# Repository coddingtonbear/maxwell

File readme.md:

# Maxwell: Bicycle Electrification

See my little blog post about this here: [http://coddingtonbear.net/maxwell-bicycle-electrification/](http://coddingtonbear.net/maxwell-bicycle-electrification/).

I have a bicycle dynamo on my bike, a rudimentary understanding of electronics, and a bunch of neopixels, gps, and bluetooth modules to use.  This is what happens when those things combine.

Maxwell is a two-part bike computer I've designed to allow me to do a few things:

* Light and control neopixel LEDs wrapped around my bike for added safety while biking at night, and added fun when biking with groups.
* Charge an easily-swappable 18650 Li-On cell for potential use when bike touring.
* Gather and transmit GPS coordinates for display on the internet somewhere.
* Display status information including my current speed, battery voltage, and current consumption, as well as disable or enable bike features including, most importantly, disabling and enabling the LEDs from a small screen mounted at the front of the bike.
* Send interesting data for display on the internet for completely impractical reasons.

The "remote" unit is based around the STM32F103CB microcontroller, and the "base" unit is based around its slightly-more-full-featured brother, the STM32F103RE.  Both communicate with one another over a CANBus (routed through two of the conductors in a length of ethernet cable) to share status information and emit/handle commands.

## Schematics

### Main

### LTE Module

### Head Unit (Remote)

## Errata

Checked items indicate errata that have been corrected in the schematic.

### Maxwell

None as of rev 1.7.

### Maxwell-remote

* [ ] Incorrect diode footprint for polarity protection.  There also might be a power deliver problem through those diodes.  Investigate that the selected mosftet is ON at Vgs -3.3.
* [ ] I think the gerbers I generated originally may have excluded the rear solder mask, as the resistors and vias were covered.
* [ ] Board-to-board interconnect should probably either not use an FPC connector, or use multiple conductors for power/ground.  I had to build a workaround connector for transferring power between the two boards.
* [ ] Resistor R2 of maxwell-remote-2 isn't really necessary; it could be connected directly to VCC.

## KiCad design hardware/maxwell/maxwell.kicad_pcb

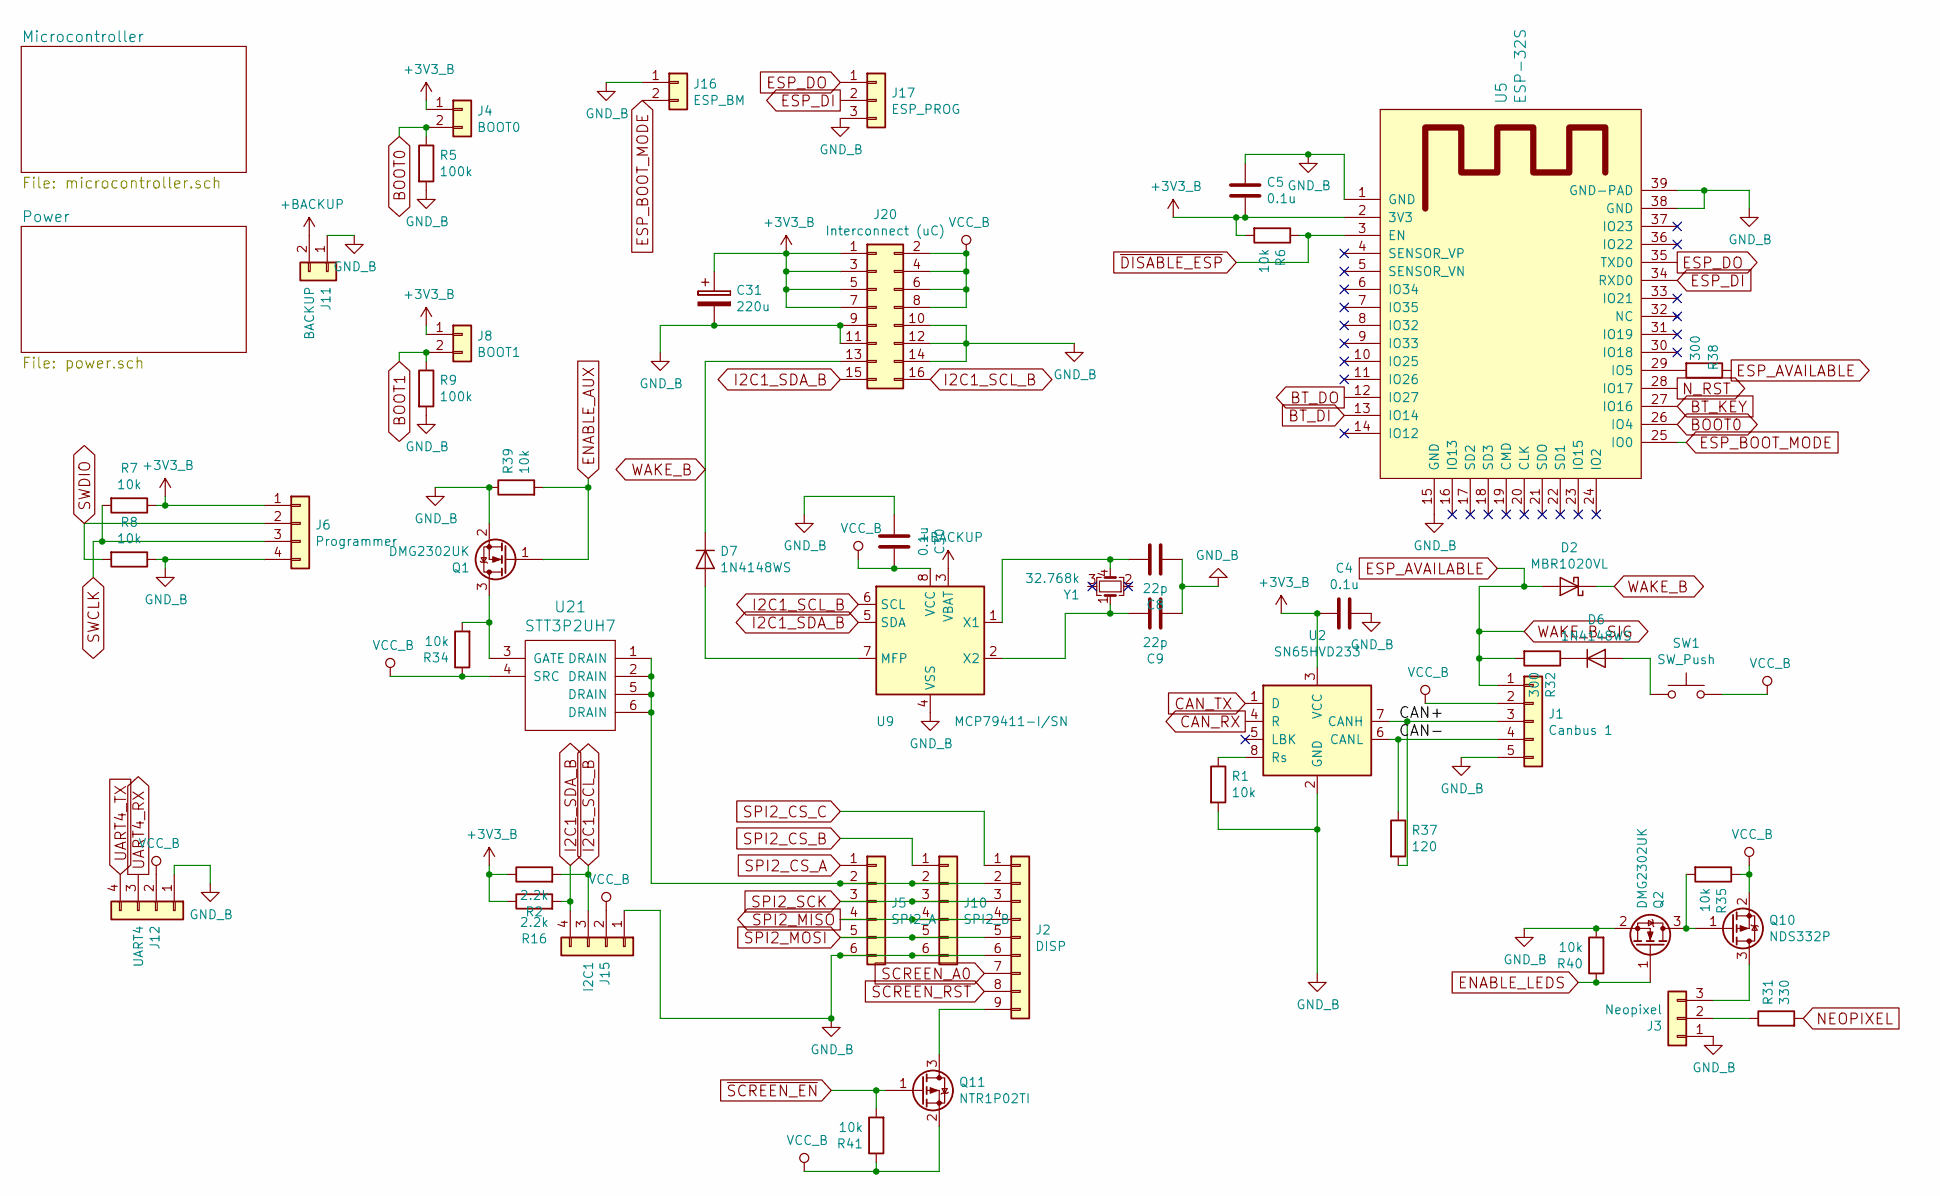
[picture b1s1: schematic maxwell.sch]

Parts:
C4, C5, C30: 0.1u; 0805_Milling
C8, C9: 22p; 0805_Milling
C31: 220u; CP_Tantalum_Case-C_EIA-6032-28_Milling
D2: MBR1020VL; D_SOD-123_LargePads
D6, D7: 1N4148WS; D_SOD-323_HandSoldering
J1: Canbus 1; JST_XH_B05B-XH-A_05x2.50mm_Straight_LargePads
J2: DISP; JST_XH_B09B-XH-A_1x09_P2.50mm_Straight_LargePads
J3: Neopixel; JST_XH_B03B-XH-A_03x2.50mm_Straight_LargePads
J4: BOOT0; Pin_Header_Straight_1x02_Pitch1.27mm_JMP
J5: SPI2_A; JST_XH_B06B-XH-A_06x2.50mm_Straight_LargePads
J6: Programmer; Pin_Header_Straight_1x04_Pitch2.54mm_LargePads
J8: BOOT1; Pin_Header_Straight_1x02_Pitch1.27mm_JMP
J10: SPI2_B; JST_XH_B06B-XH-A_06x2.50mm_Straight_LargePads
J11: BACKUP; JST_XH_B02B-XH-A_02x2.50mm_Straight_LargePads
J12: UART4; JST_XH_B04B-XH-A_04x2.50mm_Straight_LargePads
J15: I2C1; JST_XH_B04B-XH-A_04x2.50mm_Straight_LargePads
J16: ESP_BM; Pin_Header_Straight_1x02_Pitch1.27mm_JMP
J17: ESP_PROG; JST_XH_B03B-XH-A_03x2.50mm_Straight_LargePads
J20: Interconnect (uC); IDC-Header_2x08_P2.54mm_Vertical_Largepads
Q1, Q2: DMG2302UK; SOT-23_LargePads
Q10: NDS332P; SOT-23_LargePads
Q11: NTR1P02TI; SOT-23_LargePads
R1, R6, R7, R8, R34, R35, R39, R40, R41: 10k; 0805_Milling
R2, R16: 2.2k; 0805_Milling
R5, R9: 100k; 0805_Milling
R31: 330; 0805_Milling
R32, R38: 300; 0805_Milling
R37: 120; 0805_Milling
SW1: SW_Push; SMD_MINI_BLACK_TACTILE_SWITCH
U2: SN65HVD233; SOIC-8_3.9x4.9mm_P1.27mm_LargePads
U5: ESP-32S
U9: MCP79411-I/SN; SOIC-8_3.9x4.9mm_P1.27mm_LargePads
U21: STT3P2UH7; SOT-23-6_Handsoldering
Y1: 32.768k; Crystal_SMD_SeikoEpson_MC306-4Pin_8.0x3.2mm_HandSoldering

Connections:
+3V3_B: C4.2, C5.2, C31.1, J4.1, J6.1, J8.1, J20.1, J20.3, J20.5, J20.7, R2.1, R6.2, R7.1, R16.1, U2.3 (VCC), U5.2 (3V3); also elsewhere on the board
+BACKUP: J11.2, U9.3 (VBAT)
/CAN+: J1.3, R37.2, U2.7 (CANH)
/CAN-: J1.4, R37.1, U2.6 (CANL)
BOOT0: J4.2, R5.1, U5.26 (IO4); also elsewhere on the board
BOOT1: J8.2, R9.1; also elsewhere on the board
BT_DI: U5.13 (IO14); also elsewhere on the board
BT_DO: U5.12 (IO27); also elsewhere on the board
BT_KEY: U5.27 (IO16); also elsewhere on the board
CAN_RX: U2.4 (R); also elsewhere on the board
CAN_TX: U2.1 (D); also elsewhere on the board
ENABLE_AUX: Q1.1 (G), R39.2; also elsewhere on the board
ENABLE_LEDS: Q2.1 (G), R40.1; also elsewhere on the board
ESP_AVAILABLE: D2.2 (A), J1.1, R32.2, R38.1; also elsewhere on the board
ESP_BOOT_MODE: J16.2, U5.25 (IO0)
ESP_DI: J17.2, U5.34 (RXD0)
ESP_DO: J17.1, U5.35 (TXD0)
GND_B: C4.1, C5.1, C8.2, C9.2, C30.2, C31.2, J1.5, J2.6, J3.1, J5.6, J6.4, J10.6, J11.1, J12.1, J15.1, J16.1, J17.3, J20.9, J20.10, J20.11, J20.12, J20.14, Q1.2 (S), Q2.2 (S), R1.2, R5.2, R8.1, R9.2, R39.1, R40.2, U2.2 (GND), U5.1 (GND), U5.15 (GND), U5.38 (GND), U5.39 (GND-PAD), U9.4 (VSS); also elsewhere on the board
I2C1_SCL_B: J15.3, J20.16, R2.2, U9.6 (SCL); also elsewhere on the board
I2C1_SDA_B: J15.4, J20.15, R16.2, U9.5 (SDA); also elsewhere on the board
NEOPIXEL: R31.2; also elsewhere on the board
N_RST: U5.28 (IO17); also elsewhere on the board
unnamed: C8.1, U9.1 (X1), Y1.4
unnamed: C9.1, U9.2 (X2), Y1.1
unnamed: D6.1 (K), R32.1
unnamed: D6.2 (A), SW1.1
unnamed: D7.2 (A), U9.7 (MFP)
unnamed: J2.9, Q11.3 (D)
unnamed: J3.2, R31.1
unnamed: J3.3, Q10.3 (D)
unnamed: J2.2, J5.2, J10.2, U21.1 (DRAIN), U21.2 (DRAIN), U21.5 (DRAIN), U21.6 (DRAIN)
unnamed: Q1.3 (D), R34.2, U21.3 (GATE)
unnamed: Q2.3 (D), Q10.1 (G), R35.2
unnamed: R1.1, U2.8 (Rs)
unnamed: R38.2, U5.29 (IO5)
SCREEN_A0: J2.7; also elsewhere on the board
SCREEN_RST: J2.8; also elsewhere on the board
SPI2_CS_A: J5.1; also elsewhere on the board
SPI2_CS_B: J10.1; also elsewhere on the board
SPI2_CS_C: J2.1; also elsewhere on the board
SPI2_MISO: J2.4, J5.4, J10.4; also elsewhere on the board
SPI2_MOSI: J2.5, J5.5, J10.5; also elsewhere on the board
SPI2_SCK: J2.3, J5.3, J10.3; also elsewhere on the board
SWCLK: J6.3, R7.2; also elsewhere on the board
SWDIO: J6.2, R8.2; also elsewhere on the board
UART4_RX: J12.3; also elsewhere on the board
UART4_TX: J12.4; also elsewhere on the board
VCC_B: C30.1, J1.2, J12.2, J15.2, J20.2, J20.4, J20.6, J20.8, Q10.2 (S), Q11.2 (S), R34.1, R35.1, R41.1, SW1.2, U9.8 (VCC), U21.4 (SRC)
WAKE_B: D2.1 (K), D7.1 (K), J20.13
~DISABLE_ESP: R6.1, U5.3 (EN); also elsewhere on the board
~SCREEN_EN: Q11.1 (G), R41.2; also elsewhere on the board

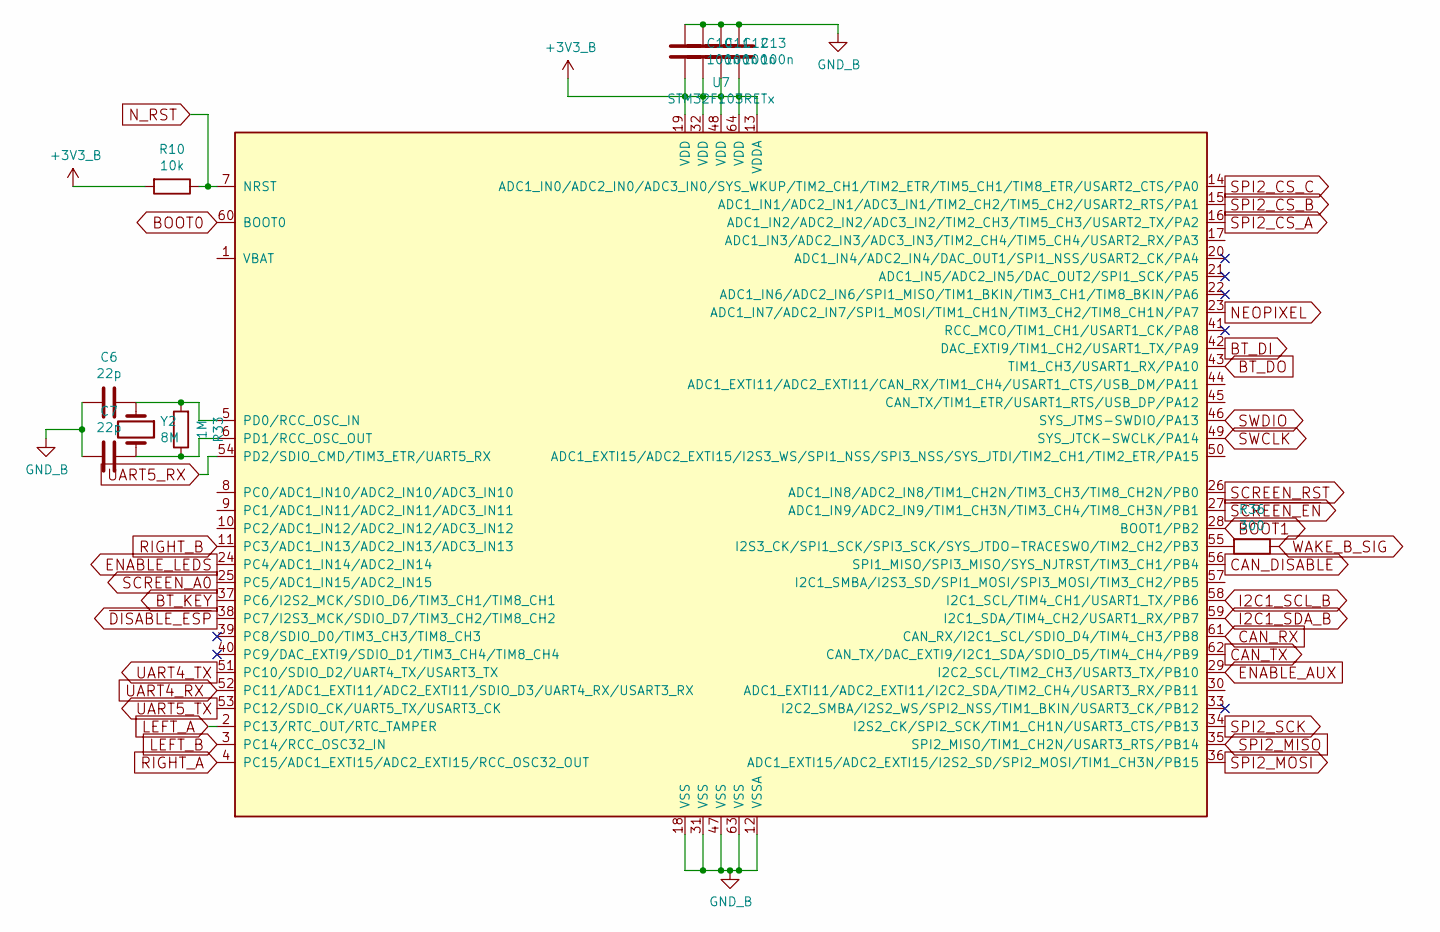
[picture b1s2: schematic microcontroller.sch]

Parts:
C6, C7: 22p; 0805_Milling
C10, C11, C12, C13: 100n; 0805_Milling
R10: 10k; 0805_Milling
R33: 1M; 0805_Milling
R36: 300; 0805_Milling
U7: STM32F103RETx; QFP64-1.27MM-CASTELLATED
Y2: 8M; Abracon-ABM2_LargePads

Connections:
+3V3_B: C10.1, C11.1, C12.1, C13.1, R10.2, U7.13 (VDDA), U7.19 (VDD), U7.32 (VDD), U7.48 (VDD), U7.64 (VDD); also elsewhere on the board
BOOT0: U7.60 (BOOT0); also elsewhere on the board
BOOT1: U7.28 (BOOT1/PB2); also elsewhere on the board
BT_DI: U7.42 (DAC_EXTI9/TIM1_CH2/USART1_TX/PA9); also elsewhere on the board
BT_DO: U7.43 (TIM1_CH3/USART1_RX/PA10); also elsewhere on the board
BT_KEY: U7.37 (PC6/I2S2_MCK/SDIO_D6/TIM3_CH1/TIM8_CH1); also elsewhere on the board
CAN_DISABLE: U7.56 (SPI1_MISO/SPI3_MISO/SYS_NJTRST/TIM3_CH1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)
CAN_RX: U7.61 (CAN_RX/I2C1_SCL/SDIO_D4/TIM4_CH3/PB8); also elsewhere on the board
CAN_TX: U7.62 (CAN_TX/DAC_EXTI9/I2C1_SDA/SDIO_D5/TIM4_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); also elsewhere on the board
ENABLE_AUX: U7.29 (I2C2_SCL/TIM2_CH3/USART3_TX/PB10); also elsewhere on the board
ENABLE_LEDS: U7.24 (PC4/ADC1_IN14/ADC2_IN14); also elsewhere on the board
ESP_AVAILABLE: R36.1; also elsewhere on the board
GND_B: C6.2, C7.2, C10.2, C11.2, C12.2, C13.2, U7.12 (VSSA), U7.18 (VSS), U7.31 (VSS), U7.47 (VSS), U7.63 (VSS); also elsewhere on the board
I2C1_SCL_B: U7.58 (I2C1_SCL/TIM4_CH1/USART1_TX/PB6); also elsewhere on the board
I2C1_SDA_B: U7.59 (I2C1_SDA/TIM4_CH2/USART1_RX/PB7); also elsewhere on the board
LEFT_A: U7.2 (PC13/RTC_OUT/RTC_TAMPER); also elsewhere on the board
LEFT_B: U7.3 (PC14/RCC_OSC32_IN); also elsewhere on the board
NEOPIXEL: U7.23 (ADC1_IN7/ADC2_IN7/SPI1_MOSI/TIM1_CH1N/T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); also elsewhere on the board
N_RST: R10.1, U7.7 (NRST); also elsewhere on the board
unnamed: C6.1, R33.2, U7.5 (PD0/RCC_OSC_IN), Y2.1
unnamed: C7.1, R33.1, U7.6 (PD1/RCC_OSC_OUT), Y2.2
unnamed: R36.2, U7.55 (I2S3_CK/SPI1_SCK/SPI3_SCK/SYS_JTDO-TRAC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)
RIGHT_A: U7.4 (PC15/ADC1_EXTI15/ADC2_EXTI15/RCC_OSC32_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); also elsewhere on the board
RIGHT_B: U7.11 (PC3/ADC1_IN13/ADC2_IN13/ADC3_IN13); also elsewhere on the board
SCREEN_A0: U7.25 (PC5/ADC1_IN15/ADC2_IN15); also elsewhere on the board
SCREEN_RST: U7.26 (ADC1_IN8/ADC2_IN8/TIM1_CH2N/TIM3_CH3/TI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); also elsewhere on the board
SPI2_CS_A: U7.16 (ADC1_IN2/ADC2_IN2/ADC3_IN2/TIM2_CH3/TIM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); also elsewhere on the board
SPI2_CS_B: U7.15 (ADC1_IN1/ADC2_IN1/ADC3_IN1/TIM2_CH2/TIM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); also elsewhere on the board
SPI2_CS_C: U7.14 (ADC1_IN0/ADC2_IN0/ADC3_IN0/SYS_WKUP/TIM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); also elsewhere on the board
SPI2_MISO: U7.35 (SPI2_MISO/TIM1_CH2N/USART3_RTS/PB14); also elsewhere on the board
SPI2_MOSI: U7.36 (ADC1_EXTI15/ADC2_EXTI15/I2S2_SD/SPI2_MO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); also elsewhere on the board
SPI2_SCK: U7.34 (I2S2_CK/SPI2_SCK/TIM1_CH1N/USART3_CTS/P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); also elsewhere on the board
SWCLK: U7.49 (SYS_JTCK-SWCLK/PA14); also elsewhere on the board
SWDIO: U7.46 (SYS_JTMS-SWDIO/PA13); also elsewhere on the board
UART4_RX: U7.52 (PC11/ADC1_EXTI11/ADC2_EXTI11/SDIO_D3/UA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); also elsewhere on the board
UART4_TX: U7.51 (PC10/SDIO_D2/UART4_TX/USART3_TX); also elsewhere on the board
UART5_RX: U7.54 (PD2/SDIO_CMD/TIM3_ETR/UART5_RX)
UART5_TX: U7.53 (PC12/SDIO_CK/UART5_TX/USART3_CK)
~DISABLE_ESP: U7.38 (PC7/I2S3_MCK/SDIO_D7/TIM3_CH2/TIM8_CH2); also elsewhere on the board
~SCREEN_EN: U7.27 (ADC1_IN9/ADC2_IN9/TIM1_CH3N/TIM3_CH4/TI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); also elsewhere on the board

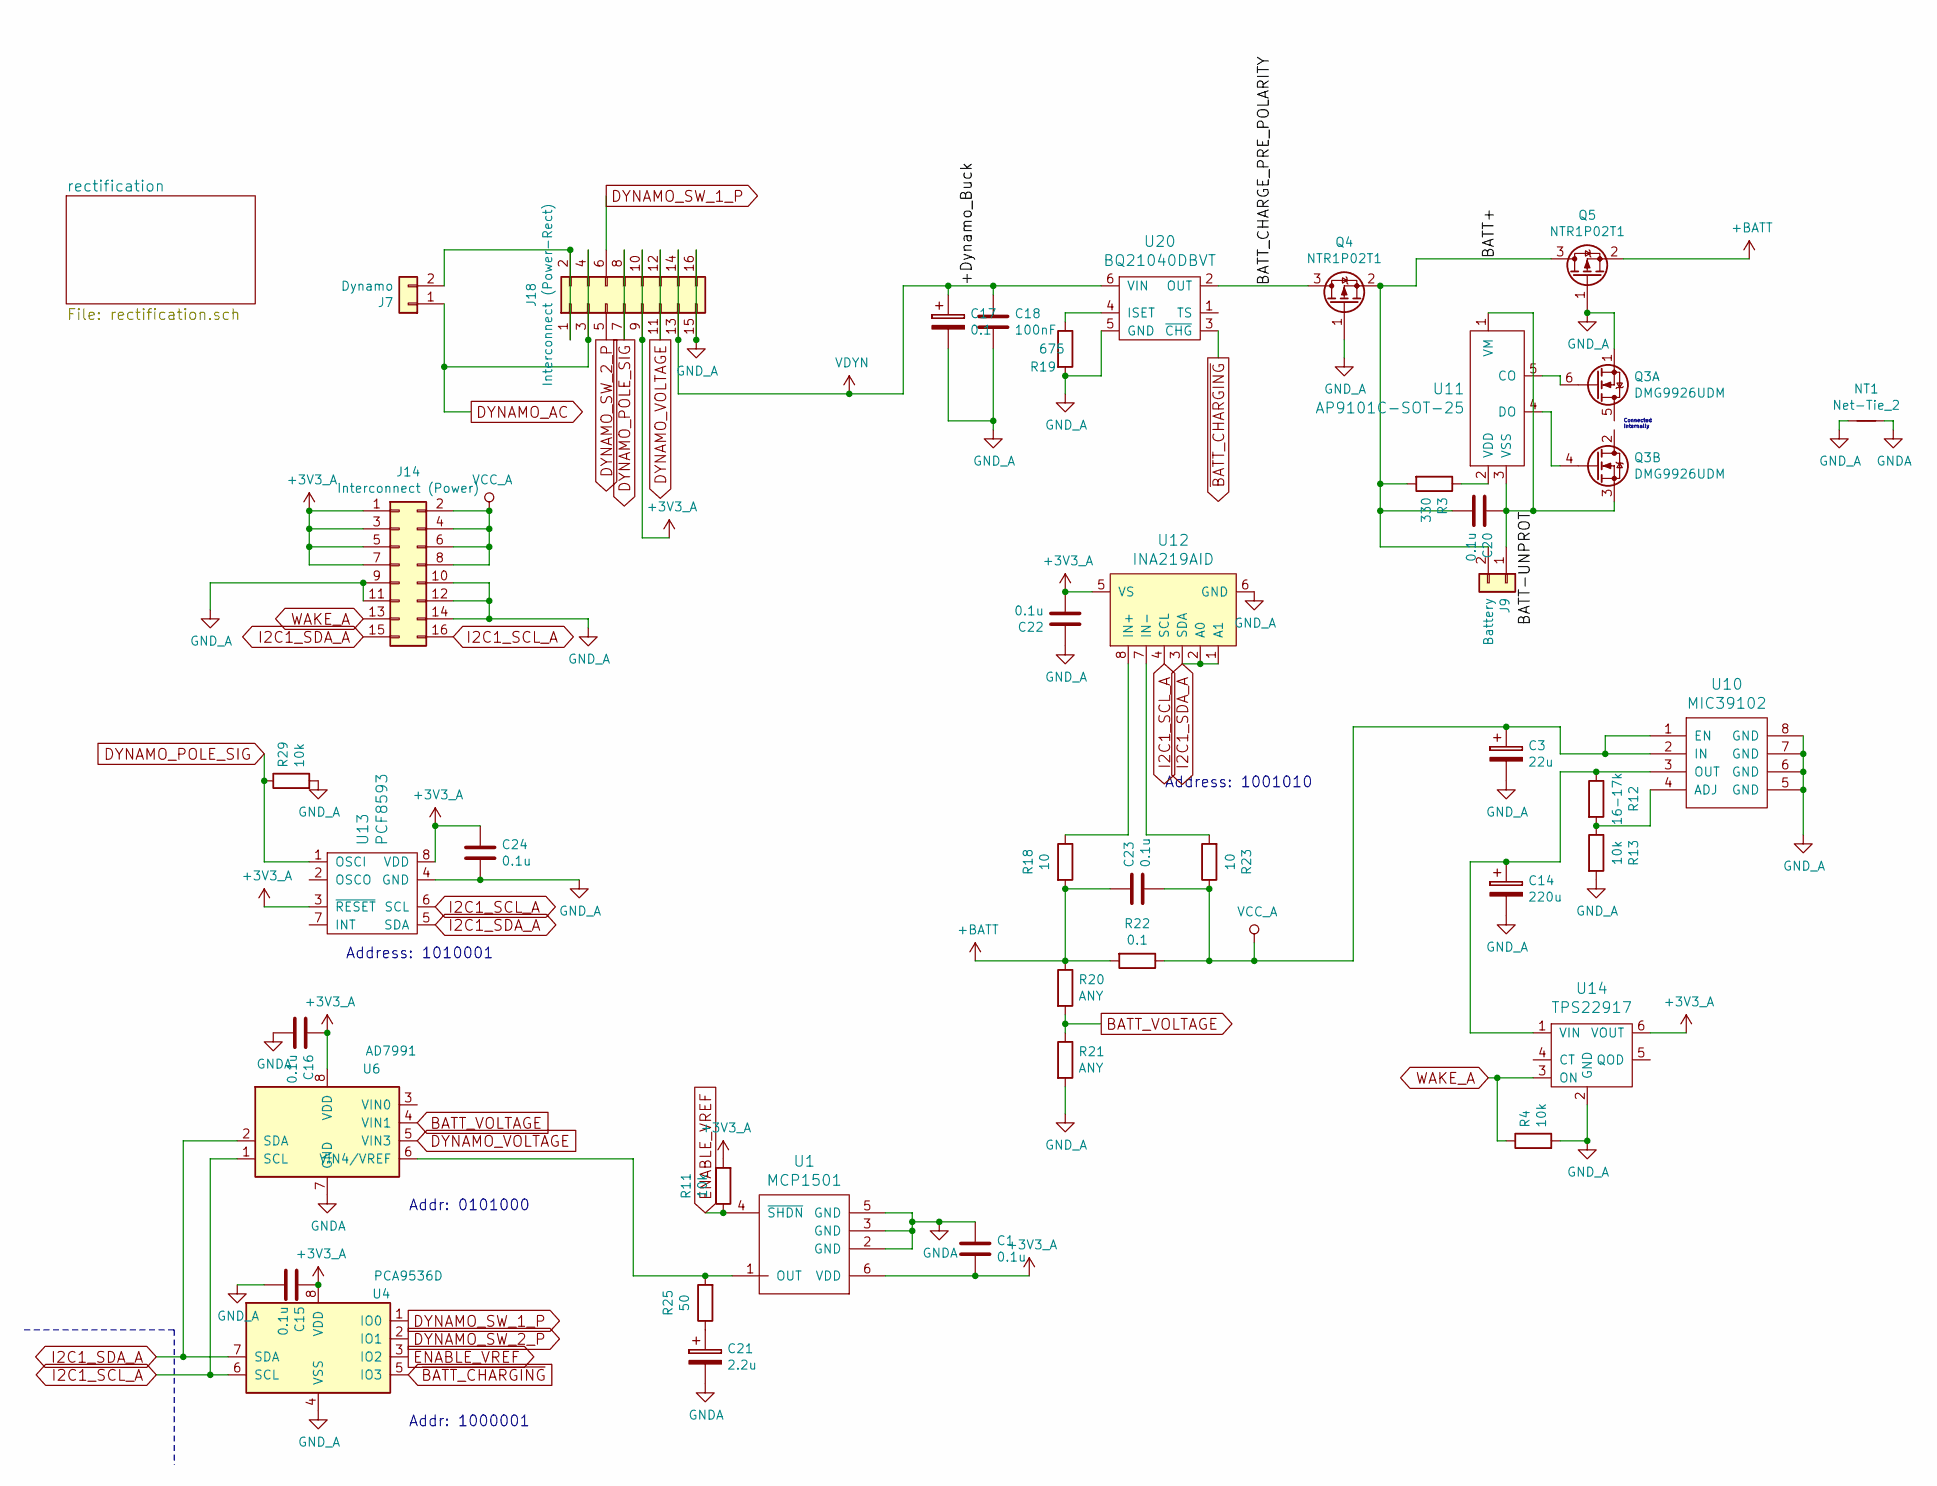
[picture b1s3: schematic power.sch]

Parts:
C1, C15, C16, C20, C22, C23, C24: 0.1u; 0805_Milling
C3: 22u; CP_Tantalum_Case-C_EIA-6032-28_Milling
C14: 220u; CP_Tantalum_Case-C_EIA-6032-28_Milling
C17: 0.1; JST_XH_B02B-XH-A_02x2.50mm_Straight_LargePads
C18: 100nF; 0805_Milling
C21: 2.2u; CP_Tantalum_Case-C_EIA-6032-28_Milling
J7: Dynamo; JST_XH_B02B-XH-A_02x2.50mm_Straight_LargePads
J9: Battery; JST_XH_B02B-XH-A_02x2.50mm_Straight_LargePads
J14: Interconnect (Power); IDC-Header_2x08_P2.54mm_Vertical_Largepads
J18: Interconnect (Power-Rect); PinHeader_2x08_P2.54mm_Vertical_LargePads
NT1: Net-Tie_2; NetTie-2_SMD_Pad0.5mm
Q3: DMG9926UDM; SOT-23-6_Handsoldering
Q4, Q5: NTR1P02T1; SOT-23_LargePads
R3: 330; 0805_Milling
R4, R11, R13, R29: 10k; 0805_Milling
R12: 16-17k; 0805_Milling
R18, R23: 10; 0805_Milling
R19: 675; 0805_Milling
R20, R21: ANY; 0805_Milling
R22: 0.1; 0805_Milling
R25: 50; 0805_Milling
U1: MCP1501; TSOT-23-6_HandSoldering
U4: PCA9536D; SOIC-8_3.9x4.9mm_P1.27mm_LargePads
U6: AD7991; SOT-23-8_Handsoldering
U10: MIC39102; SOIC-8_3.9x4.9mm_P1.27mm_LargePads
U11: AP9101C-SOT-25; SOT-23-5_HandSoldering
U12: INA219AID; SOIC-8_3.9x4.9mm_P1.27mm_LargePads; MPN INA219AIDCNR; Digi-Key_PN 296-23770-1-ND
U13: PCF8593; SOIC-8_3.9x4.9mm_P1.27mm_LargePads
U14: TPS22917; SOT-23-6_Handsoldering
U20: BQ21040DBVT; SOT-23-6_Handsoldering

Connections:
+3V3_U: C14.1, R12.1, U10.3 (OUT), U14.1 (VIN)
+BATT: C23.2, Q5.2 (S), R18.2, R20.1, R22.2
/Power/BATT+: C20.1, J9.2, Q4.2 (S), Q5.3 (D), R3.2
/Power/BATT-UNPROT: C20.2, J9.1, Q3.3 (S), U11.1 (VM), U11.3 (VSS)
/Power/BATT_CHARGE_PRE_POLARITY: Q4.3 (D), U20.2 (OUT)
BATT_VOLTAGE: R20.2, R21.1, U6.4 (VIN1)
CHARGE_VOLTAGE: J18.11, J18.12, U6.5 (VIN3)
DYNAMO_AC: J7.1, J18.3, J18.4
DYNAMO_POLE_SIG: J18.7, J18.8, R29.1, U13.1 (OSCI)
GNDA: C1.2, C16.1, C21.2, NT1.2, U1.2 (GND), U1.3 (GND), U1.5 (GND), U6.7 (GND)
GND_A: C3.2, C14.2, C15.1, C17.2, C18.1, C22.2, C24.1, J14.9, J14.10, J14.11, J14.12, J14.14, J18.15, J18.16, NT1.1, Q3.1 (S), Q4.1 (G), Q5.1 (G), R4.2, R13.2, R19.2, R21.2, R29.2, U4.4 (VSS), U10.5 (GND), U10.6 (GND), U10.7 (GND), U10.8 (GND), U12.6 (GND), U13.4 (GND), U14.2 (GND), U20.5 (GND); also elsewhere on the board
I2C1_SCL_A: J14.16, U4.6 (SCL), U6.1 (SCL), U12.4 (SCL), U13.6 (SCL); also elsewhere on the board
I2C1_SDA_A: J14.15, U4.7 (SDA), U6.2 (SDA), U12.1 (A1), U12.2 (A0), U12.3 (SDA), U13.5 (SDA); also elsewhere on the board
unnamed: C21.1, R25.1
unnamed: J7.2, J18.1, J18.2
unnamed: Q3.4 (G), U11.4 (DO)
unnamed: Q3.6 (G), U11.5 (CO)
unnamed: R3.1, U11.2 (VDD)
unnamed: R12.2, R13.1, U10.4 (ADJ)
unnamed: R18.1, U12.8 (IN+)
unnamed: R19.1, U20.4 (ISET)
unnamed: R23.2, U12.7 (IN-)
unnamed: R25.2, U1.1 (OUT), U6.6 (VIN4/VREF)
VCC_A: C3.1, C23.1, J14.2, J14.4, J14.6, J14.8, R22.1, R23.1, U10.1 (EN), U10.2 (IN)
VDYN: C17.1, C18.2, J18.13, J18.14, U20.6 (VIN)
WAKE_A: J14.13, R4.1, U14.3 (ON)

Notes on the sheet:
Addr: 1000001
Addr: 0101000
Connected Internally
Address: 1001010
Address: 1010001

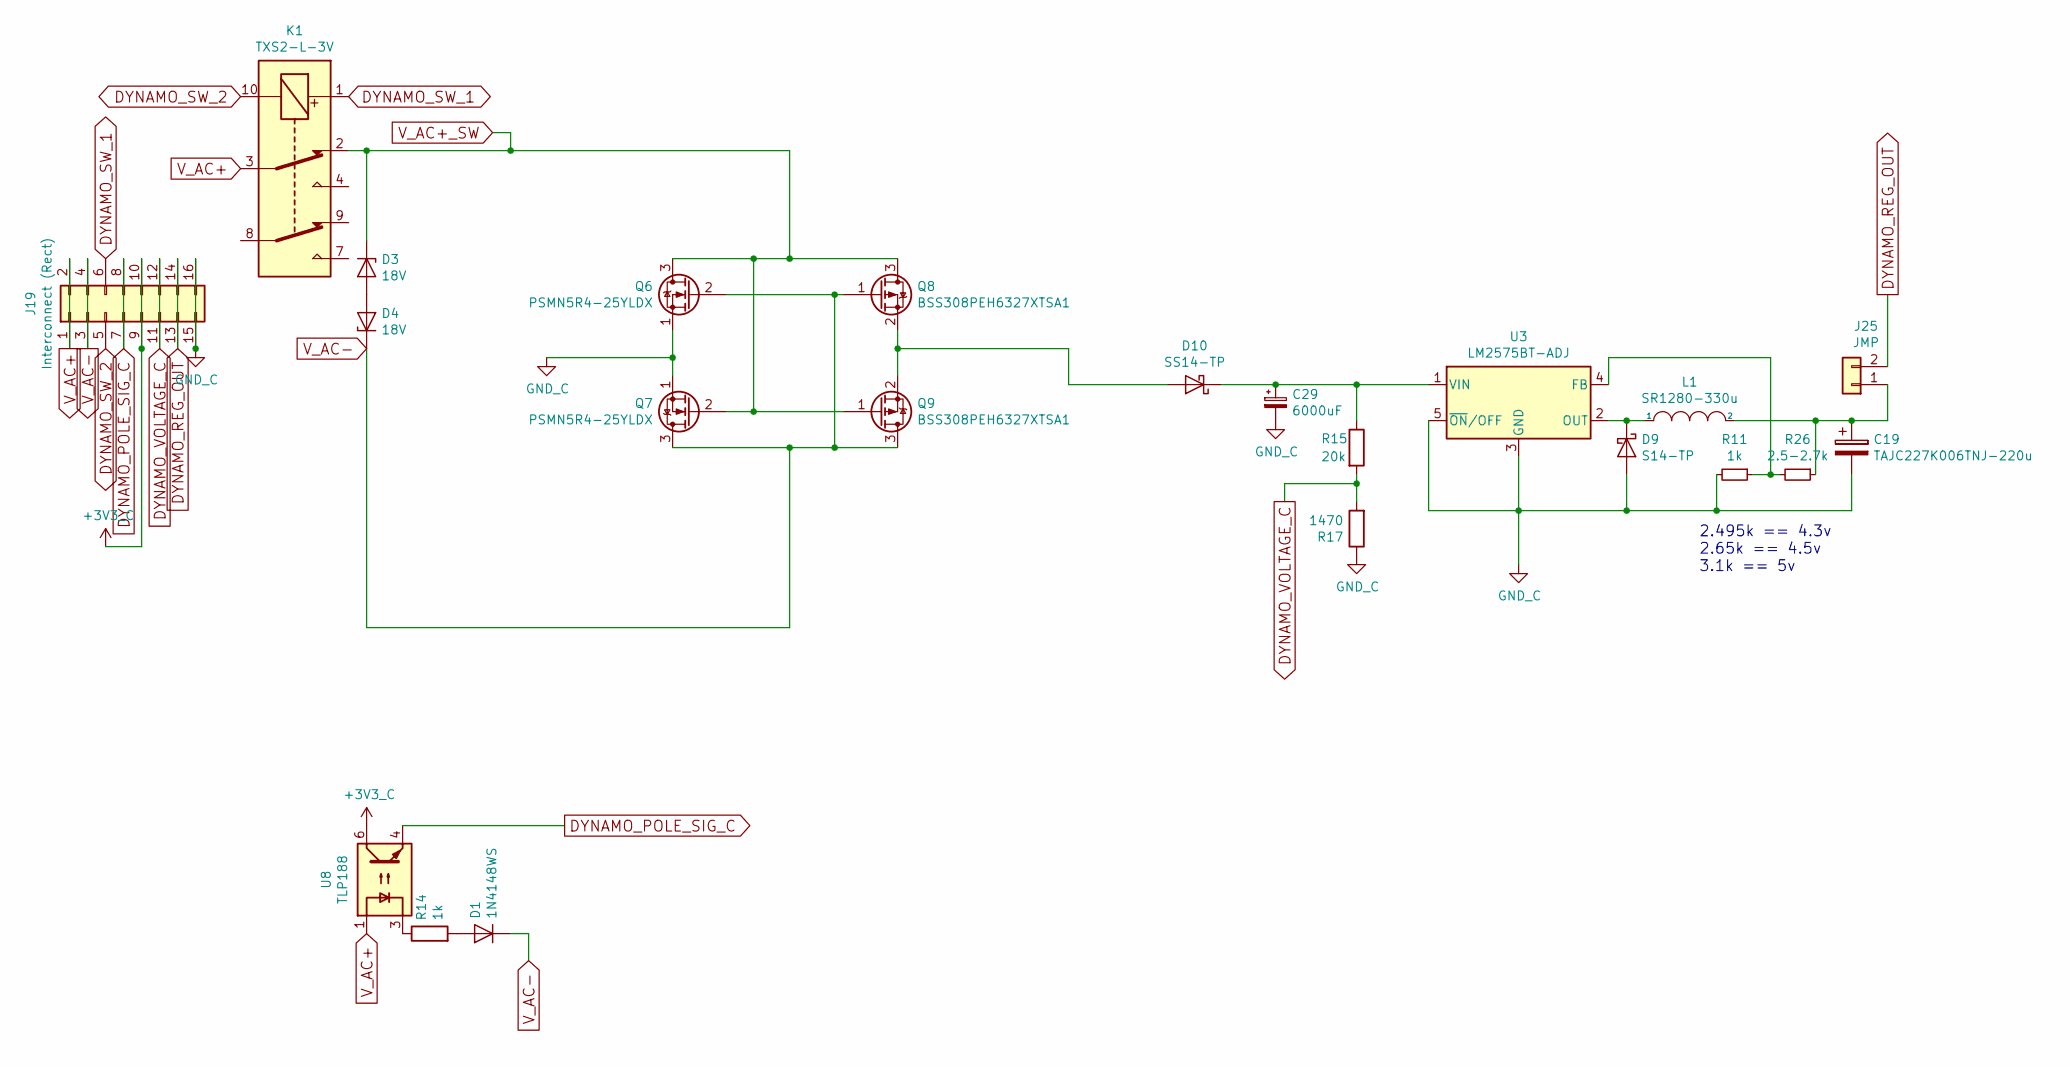
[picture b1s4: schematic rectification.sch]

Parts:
C19: TAJC227K006TNJ-220u; CP_Tantalum_Case-C_EIA-6032-28_Milling
C29: 6000uF; JST_XH_B02B-XH-A_02x2.50mm_Straight_LargePads
D1: 1N4148WS; D_SOD-323_HandSoldering
D3, D4: 18V; D_DO-201AE_P15.24mm_Horizontal
D9: S14-TP; DO-214AC
D10: SS14-TP; DO-214AC
J19: Interconnect (Rect); PinHeader_2x08_P2.54mm_Vertical_LargePads
J25: JMP; PinHeader_1x02_P2.54mm_Vertical
K1: TXS2-L-3V; Panasonic_TX-S_DPDT
L1: SR1280-330u; SRF1280-PARALLEL
Q6, Q7: PSMN5R4-25YLDX; PSMN5R4-25YLD
Q8, Q9: BSS308PEH6327XTSA1; SOT-23_LargePads
R11, R14: 1k; 0805_Milling
R15: 20k; 0805_Milling
R17: 1470; 0805_Milling
R26: 2.5-2.7k; 0805_Milling
U3: LM2575BT-ADJ; TO-263-5_TabPin3
U8: TLP188; SO-4_Optocoupler_Milling

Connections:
+3V3_C: J19.9, J19.10, U8.6
DYNAMO_POLE_SIG_C: J19.7, J19.8, U8.4
DYNAMO_REG_OUT: J19.13, J19.14, J25.2
DYNAMO_SW_1: J19.6, K1.1
DYNAMO_SW_2: J19.5, K1.10
DYNAMO_VOLTAGE_C: J19.11, J19.12, R15.2, R17.2
unnamed: C19.1, J25.1, L1.2, R26.1
unnamed: C29.1, D10.1 (K), R15.1, U3.1 (VIN)
unnamed: D1.2 (A), R14.2
unnamed: D3.2 (A), D4.2 (A)
unnamed: D9.1 (K), L1.1, U3.2 (OUT)
unnamed: D10.2 (A), Q8.2 (S), Q9.2 (S)
unnamed: R14.1, U8.3
V_AC+: J19.1, J19.2, K1.3, U8.1
V_AC+_SW: D3.1 (K), K1.2, Q6.3 (D), Q7.2 (G), Q8.3 (D), Q9.1 (G)
V_AC-: D1.1 (K), D4.1 (K), J19.3, J19.4, Q6.2 (G), Q7.3 (D), Q8.1 (G), Q9.3 (D)

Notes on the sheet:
2.495k == 4.3v 2.65k == 4.5v 3.1k == 5v

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
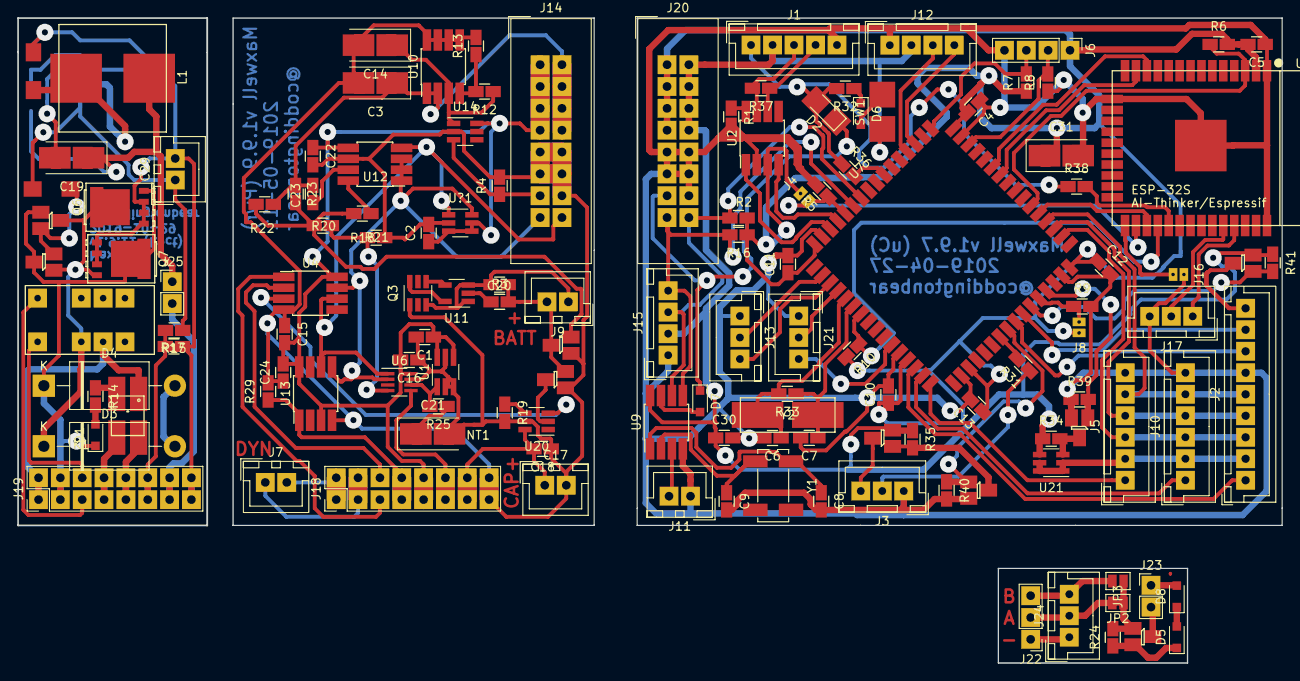
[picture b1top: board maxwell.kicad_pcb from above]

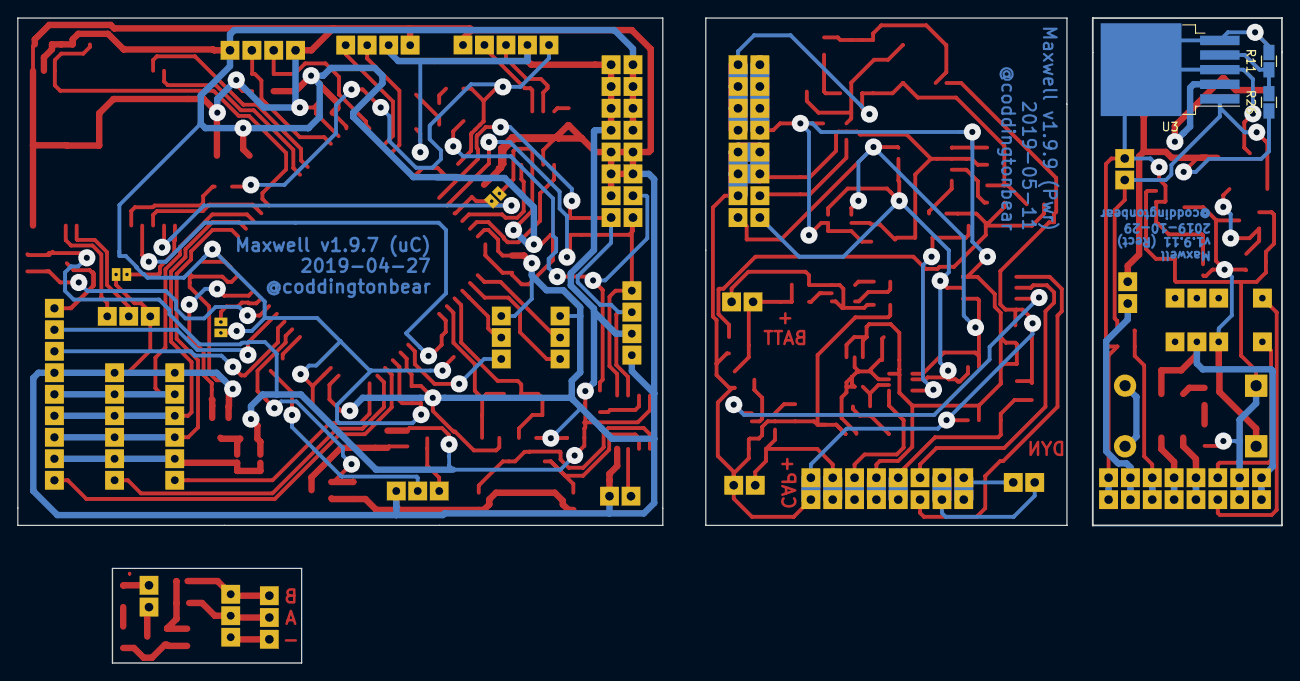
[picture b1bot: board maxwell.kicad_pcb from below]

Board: 2 copper layers, 147.0 x 75.0 mm, 137 parts (3 on the bottom side), 114 nets.

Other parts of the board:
C2: 0.1u; 0805_Milling
D5, D8: 1N4148WS; D_SOD-323_HandSoldering
J13: Ctrl_L; JST_XH_B03B-XH-A_03x2.50mm_Straight_LargePads
J21: Ctrl_R; JST_XH_B03B-XH-A_03x2.50mm_Straight_LargePads
J22: To Board; PinHeader_1x03_P2.54mm_Vertical
J23: CAN; PinHeader_1x02_P2.54mm_Vertical
J24: From Button; JST_XH_B03B-XH-A_03x2.50mm_Straight_LargePads
JP2: JMP_A; SolderJumper-2_P1.3mm_Bridged_Pad1.0x1.5mm
JP3: JMP_B; SolderJumper-2_P1.3mm_Open_Pad1.0x1.5mm
Q12: NTR1P02T1; SOT-23_LargePads
R24: 10k; 0805_Milling
U?1: TMP100; SOT-23-6_Handsoldering

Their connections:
GND_A: C2.2, U?1.2; also elsewhere on the board
GND_B: J13.1, J21.1; also elsewhere on the board
I2C1_SCL_A: U?1.1; also elsewhere on the board
I2C1_SDA_A: U?1.6; also elsewhere on the board
LEFT_A: J13.2; also elsewhere on the board
LEFT_B: J13.3; also elsewhere on the board
unnamed: D5.1, Q12.2, R24.1
unnamed: D5.2, D8.1
unnamed: D8.2, J23.1
unnamed: J22.1, J24.1
unnamed: J22.2, J24.2, JP2.2
unnamed: J22.3, J24.3, JP3.2
unnamed: J23.2, Q12.3
unnamed: JP2.1, JP3.1, Q12.1, R24.2
RIGHT_A: J21.2; also elsewhere on the board
RIGHT_B: J21.3; also elsewhere on the board

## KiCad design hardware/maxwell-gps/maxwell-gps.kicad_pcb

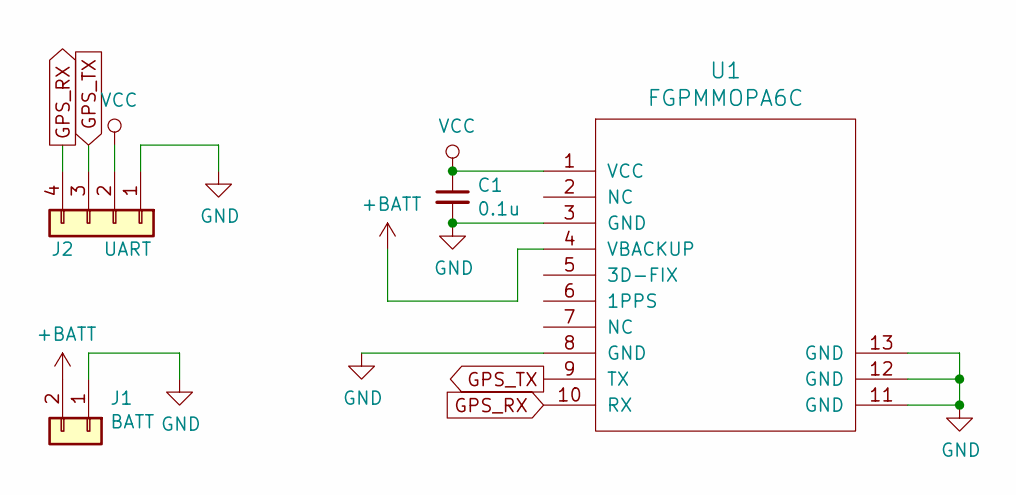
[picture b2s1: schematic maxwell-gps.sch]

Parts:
C1: 0.1u; 0805_Milling
J1: BATT; JST_XH_B02B-XH-A_02x2.50mm_Straight_LargePads
J2: UART; JST_XH_B04B-XH-A_04x2.50mm_Straight_LargePads
U1: FGPMMOPA6C

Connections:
+BATT: J1.2, U1.4 (VBACKUP)
GND: C1.2, J1.1, J2.1, U1.3 (GND), U1.8 (GND), U1.11 (GND), U1.12 (GND), U1.13 (GND)
GPS_RX: J2.4, U1.10 (RX)
GPS_TX: J2.3, U1.9 (TX)
VCC: C1.1, J2.2, U1.1 (VCC)

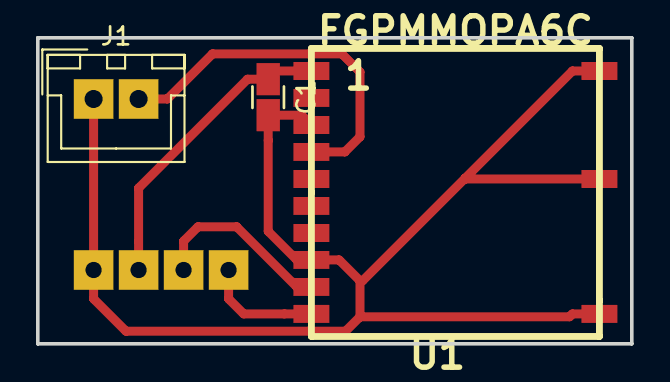
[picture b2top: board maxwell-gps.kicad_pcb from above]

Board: 2 copper layers, 33.0 x 17.0 mm, 4 parts (1 on the bottom side), 5 nets.
